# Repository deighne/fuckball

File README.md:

# FUCKBALL

This trackball is my update and twist on [Brickbots' aball](https://github.com/brickbots/aball) with a lot of inspiration from the [Ploopy Adept](https://github.com/ploopyco/adept-trackball). 

The biggest changes are:

- Built to use PMW3360 / PMW3389 breakout boards
- RP2040-Zero Board to keep things small and modern
- Footprint designed to sit alongside [Sofle v2](https://github.com/josefadamcik/SofleKeyboard) on either side
- A single button, as a treat

## What's the point?

I really like the simplicity of the aball design, but found its quirks kind of irritating to build. Elite-C boards aren't cheap compared to the thousands of nano boards on the market, and handwiring tiny tiny cables leaves a lot of room for error. I felt like there wasn't a great option for a buttonless trackball with a high precision sensor; the Ploopy nano is solidly entry-level, and nicer options like the Ploopy Adept are comparitively big and bulky. I think this strikes a nice balance.

## Why the breakout board and not sensor only? 

At the time of writing (December 2024), the cost difference between just a PMW3389 sensor and the sensor + breakout board with presoldered pins is just a few bucks; it's cheaper to buy the board than to get a custom PCB with assembly like the [Jfedor2 RP2040 + PMW3360 board](https://github.com/jfedor2/rp2040-pmw3360). That should make this more flexible to use other sensors in the future with the same breakout!

## License etc.

GPLv3! Do something weird with this design please.

## Fuckball?

The name wasn't already taken?

## Status

- Gerber files and Kicad are a prototype design; has not yet been printed. No guarantees! (There never are with open source any way)
- Needs BOM, guide, etc. etc. 

## Sources and Inspiration

- [Aball](https://github.com/brickbots/aball)
- [Ploopy Adept](https://github.com/ploopyco/adept-trackball))
- [Sofle](https://github.com/josefadamcik/SofleKeyboard)
- [RP2040+PMW3360](https://github.com/jfedor2/rp2040-pmw3360)

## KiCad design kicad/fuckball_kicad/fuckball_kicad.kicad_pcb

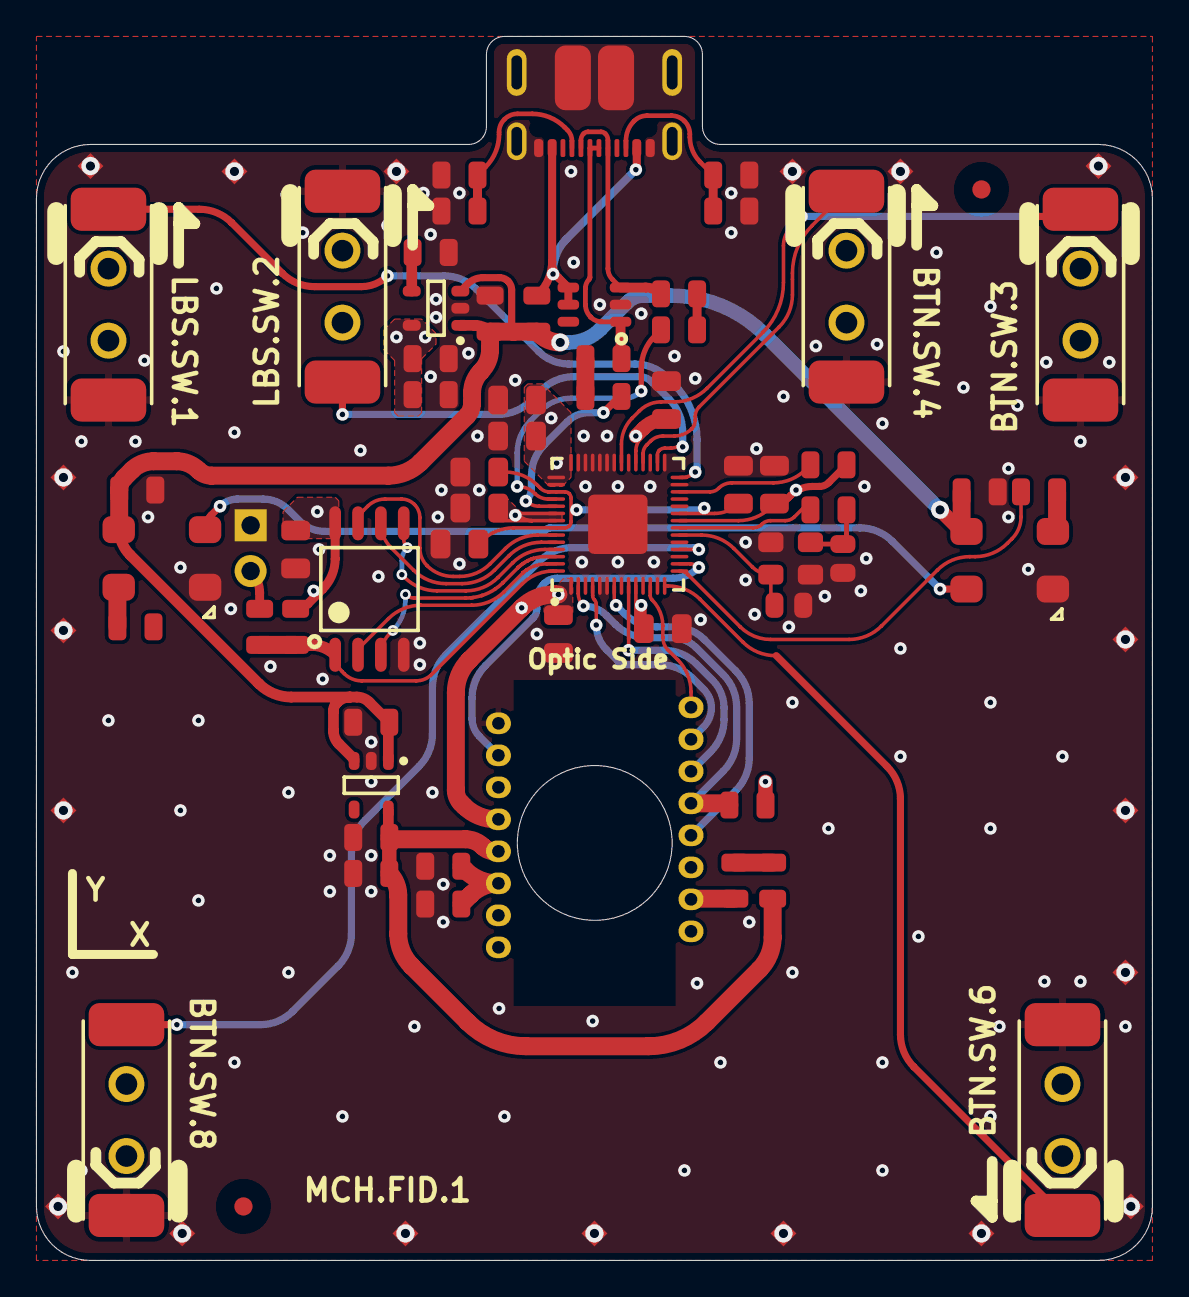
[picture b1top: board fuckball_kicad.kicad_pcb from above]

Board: 4 copper layers, 62.0 x 68.0 mm, 82 parts (1 on the bottom side), 45 nets.

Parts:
BTN.SW.3, BTN.SW.4, BTN.SW.6, BTN.SW.8: D2LS-21
LBS.SW.1, LBS.SW.2: D2LS-21
LED.C.20, LED.C.23, LED.R.9, LED.R.16: 0805
LED.D.1, LED.D.3: IN-PI55TATPRPGPB
MCH.FID.1, MCH.FID.2: IPC-7351 Fiducial 1mm; FIDUCIAL_1.5
MCH.LOGO.2: Coordinate system marker for assembly; Coordinate System
MCH.SP.1, MCH.SP.2, MCH.SP.3, MCH.SP.4, MCH.SP.5, MCH.SP.6, MCH.SP.7, MCH.SP.8, MCH.SP.9, MCH.SP.10, MCH.SP.11, MCH.SP.12, MCH.SP.13, MCH.SP.14, MCH.SP.15, MCH.SP.16, MCH.SP.17, MCH.SP.18, MCH.SP.19, MCH.SP.20: Spark Gap; SparkGap
MCU.C.1, MCU.C.2, MCU.C.3, MCU.C.4, MCU.C.5, MCU.C.6, MCU.C.7, MCU.C.8, MCU.C.21, MCU.C.22, MCU.C.24: 0805 X5R; 0805 - TALL
MCU.C.9, MCU.C.19: 0603
MCU.J.1: HEADER2; 2x1
MCU.R.1, MCU.R.2, MCU.R.11, MCU.R.17: 0805
MCU.U.1: W25Q16JVSSIQ; W25Q128JVS - SOIC127P790X216-8M
MCU.U.5: RP2040; RP2040 - QFN40P700X700X90_HS-57M
MCU.Y.1: RH100-12.000-16-3030
MOS.C.10, MOS.C.11, MOS.R.3, MOS.R.4, MOS.R.5: 0805
MOS.U.2: PMW3360DM-T2QU
REG.C.12, REG.C.13, REG.C.14, REG.C.15, REG.C.16, REG.C.17, REG.C.18: 0805
REG.U.3: AP2202K-3.3; AP2202 - SOT95P270X145-5N
REG.U.4: AP2204K-1.8; AP2202 - SOT95P270X145-5N
USB.FB.1, USB.FB.2, USB.FB.3: ACML-0805-601-T; 0805
USB.J.3: DX07S016JA1R1500
USB.R.6, USB.R.7, USB.R.12, USB.R.13, USB.R.14, USB.R.15: 0805
USB.Z.1: IP4220CZ6,125; PESD3V3S4UD - SOT95P275X110-6N

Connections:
1V1: MCU.C.21.2, MCU.C.22.2, MCU.C.24.2, MCU.U.5.23, MCU.U.5.45, MCU.U.5.50
1V8: MOS.R.3.2, MOS.U.2.4, REG.C.17.2, REG.C.18.2, REG.U.4.5
3V3: MCU.C.1.2, MCU.C.2.2, MCU.C.3.2, MCU.C.4.2, MCU.C.5.2, MCU.C.6.2, MCU.C.7.2, MCU.C.8.2, MCU.R.2.1, MCU.R.17.1, MCU.U.1.8, MCU.U.5.1, MCU.U.5.10, MCU.U.5.22, MCU.U.5.33, MCU.U.5.42, MCU.U.5.43, MCU.U.5.44, MCU.U.5.48, MCU.U.5.49, MOS.R.5.2, MOS.U.2.5, REG.C.13.2, REG.C.14.2, REG.U.3.5
GND: BTN.SW.3.B, BTN.SW.4.B, BTN.SW.6.B, BTN.SW.8.A, LBS.SW.1.B, LBS.SW.2.A, LED.C.20.1, LED.C.23.1, LED.D.1.3, LED.D.3.3, MCH.SP.1.1, MCH.SP.2.1, MCH.SP.3.1, MCH.SP.4.1, MCH.SP.5.1, MCH.SP.6.1, MCH.SP.7.1, MCH.SP.8.1, MCH.SP.9.1, MCH.SP.10.1, MCH.SP.11.1, MCH.SP.12.1, MCH.SP.13.1, MCH.SP.14.1, MCH.SP.15.1, MCH.SP.16.1, MCH.SP.17.1, MCH.SP.18.1, MCH.SP.19.1, MCH.SP.20.1, MCU.C.1.1, MCU.C.2.1, MCU.C.3.1, MCU.C.4.1, MCU.C.5.1, MCU.C.6.1, MCU.C.7.1, MCU.C.8.1, MCU.C.9.2, MCU.C.19.1, MCU.C.21.1, MCU.C.22.1, MCU.C.24.1, MCU.J.1.1, MCU.U.1.4, MCU.U.5.3, MCU.U.5.5, MCU.U.5.6, MCU.U.5.8, MCU.U.5.11, MCU.U.5.13, MCU.U.5.17, MCU.U.5.19, MCU.U.5.27, MCU.U.5.29, MCU.U.5.31, MCU.U.5.34, MCU.U.5.36, MCU.U.5.37, MCU.U.5.38, MCU.U.5.39, MCU.U.5.40, MCU.U.5.41, MCU.U.5.57, MCU.Y.1.2, MCU.Y.1.4, MOS.C.10.1, MOS.C.11.1, MOS.U.2.8, REG.C.12.1, REG.C.13.1, REG.C.14.1, REG.C.15.1, REG.C.16.1, REG.C.17.1, REG.C.18.1, REG.U.3.2, REG.U.4.2, USB.J.3.1, USB.J.3.12, USB.J.3.SHELL, USB.R.12.1, USB.R.13.1, USB.R.14.1, USB.R.15.1, USB.Z.1.2
LEDData: LED.R.16.2, MCU.U.5.15
NetBTN.SW.3_A: BTN.SW.3.A, MCU.U.5.35
NetBTN.SW.4_A: BTN.SW.4.A, MCU.U.5.32
NetBTN.SW.6_A: BTN.SW.6.A, MCU.U.5.14
NetBTN.SW.8_B: BTN.SW.8.B, MCU.U.5.18
NetLBS.SW.1_A: LBS.SW.1.A, MCU.U.5.28
NetLBS.SW.2_B: LBS.SW.2.B, MCU.U.5.30
NetLED.D.1_2: LED.D.1.2, LED.D.3.4
NetLED.D.1_4: LED.D.1.4, LED.R.16.1
NetLED.D.3_2: LED.D.3.2, LED.R.9.2
NetMCU.C.9_1: MCU.C.9.1, MCU.U.5.20, MCU.Y.1.1
NetMCU.C.19_2: MCU.C.19.2, MCU.R.11.2, MCU.Y.1.3
NetMCU.J.1_2: MCU.J.1.2, MCU.R.1.1
NetMCU.R.1_2: MCU.R.1.2, MCU.R.2.2, MCU.U.1.1, MCU.U.5.56
NetMCU.R.11_1: MCU.R.11.1, MCU.U.5.21
NetMCU.R.17_2: MCU.R.17.2, MCU.U.5.26
NetMCU.U.1_2: MCU.U.1.2, MCU.U.5.55
NetMCU.U.1_3: MCU.U.1.3, MCU.U.5.54
NetMCU.U.1_5: MCU.U.1.5, MCU.U.5.53
NetMCU.U.1_6: MCU.U.1.6, MCU.U.5.52
NetMCU.U.1_7: MCU.U.1.7, MCU.U.5.51
NetMCU.U.5_2: MCU.U.5.2, MOS.R.5.1, MOS.U.2.12
NetMCU.U.5_4: MCU.U.5.4, MOS.U.2.10
NetMCU.U.5_7: MCU.U.5.7, MOS.U.2.13
NetMCU.U.5_9: MCU.U.5.9, MOS.U.2.11
NetMCU.U.5_12: MCU.U.5.12, MOS.U.2.9
NetMCU.U.5_16: MCU.U.5.16, MOS.U.2.7
NetMCU.U.5_46: MCU.U.5.46, USB.R.6.2
NetMCU.U.5_47: MCU.U.5.47, USB.R.7.2
NetMOS.C.10_2: MOS.C.10.2, MOS.C.11.2, MOS.U.2.3
NetMOS.R.3_1: MOS.R.3.1, MOS.R.4.2
NetMOS.R.4_1: MOS.R.4.1, MOS.U.2.15
NetREG.C.15_2: REG.C.15.2, REG.U.3.4
NetUSB.FB.1_1: USB.FB.1.1, USB.J.3.2, USB.J.3.11, USB.Z.1.4, USB.Z.1.5
NetUSB.FB.2_1: USB.FB.2.1, USB.J.3.5, USB.J.3.8, USB.Z.1.3
NetUSB.FB.2_2: USB.FB.2.2, USB.R.6.1
NetUSB.FB.3_1: USB.FB.3.1, USB.J.3.6, USB.J.3.7, USB.Z.1.1
NetUSB.FB.3_2: USB.FB.3.2, USB.R.7.1
NetUSB.J.3_3: USB.J.3.3, USB.R.14.2, USB.R.15.2
NetUSB.J.3_9: USB.J.3.9, USB.R.12.2, USB.R.13.2
V_USB: LED.C.20.2, LED.C.23.2, LED.D.1.1, LED.D.3.1, REG.C.12.2, REG.C.16.2, REG.U.3.1, REG.U.3.3, REG.U.4.1, REG.U.4.3, USB.FB.1.2

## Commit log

2024-12-31 v. 0.001 - just cleaning up the rep
2025-01-02 v. 0.002
2025-01-02 v. 0.01

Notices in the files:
kicad/fuckball_kicad/fuckball_kicad.kicad_pcb:
Licensed under the
CERN-OHL-S v2
Copyright Ploopy
